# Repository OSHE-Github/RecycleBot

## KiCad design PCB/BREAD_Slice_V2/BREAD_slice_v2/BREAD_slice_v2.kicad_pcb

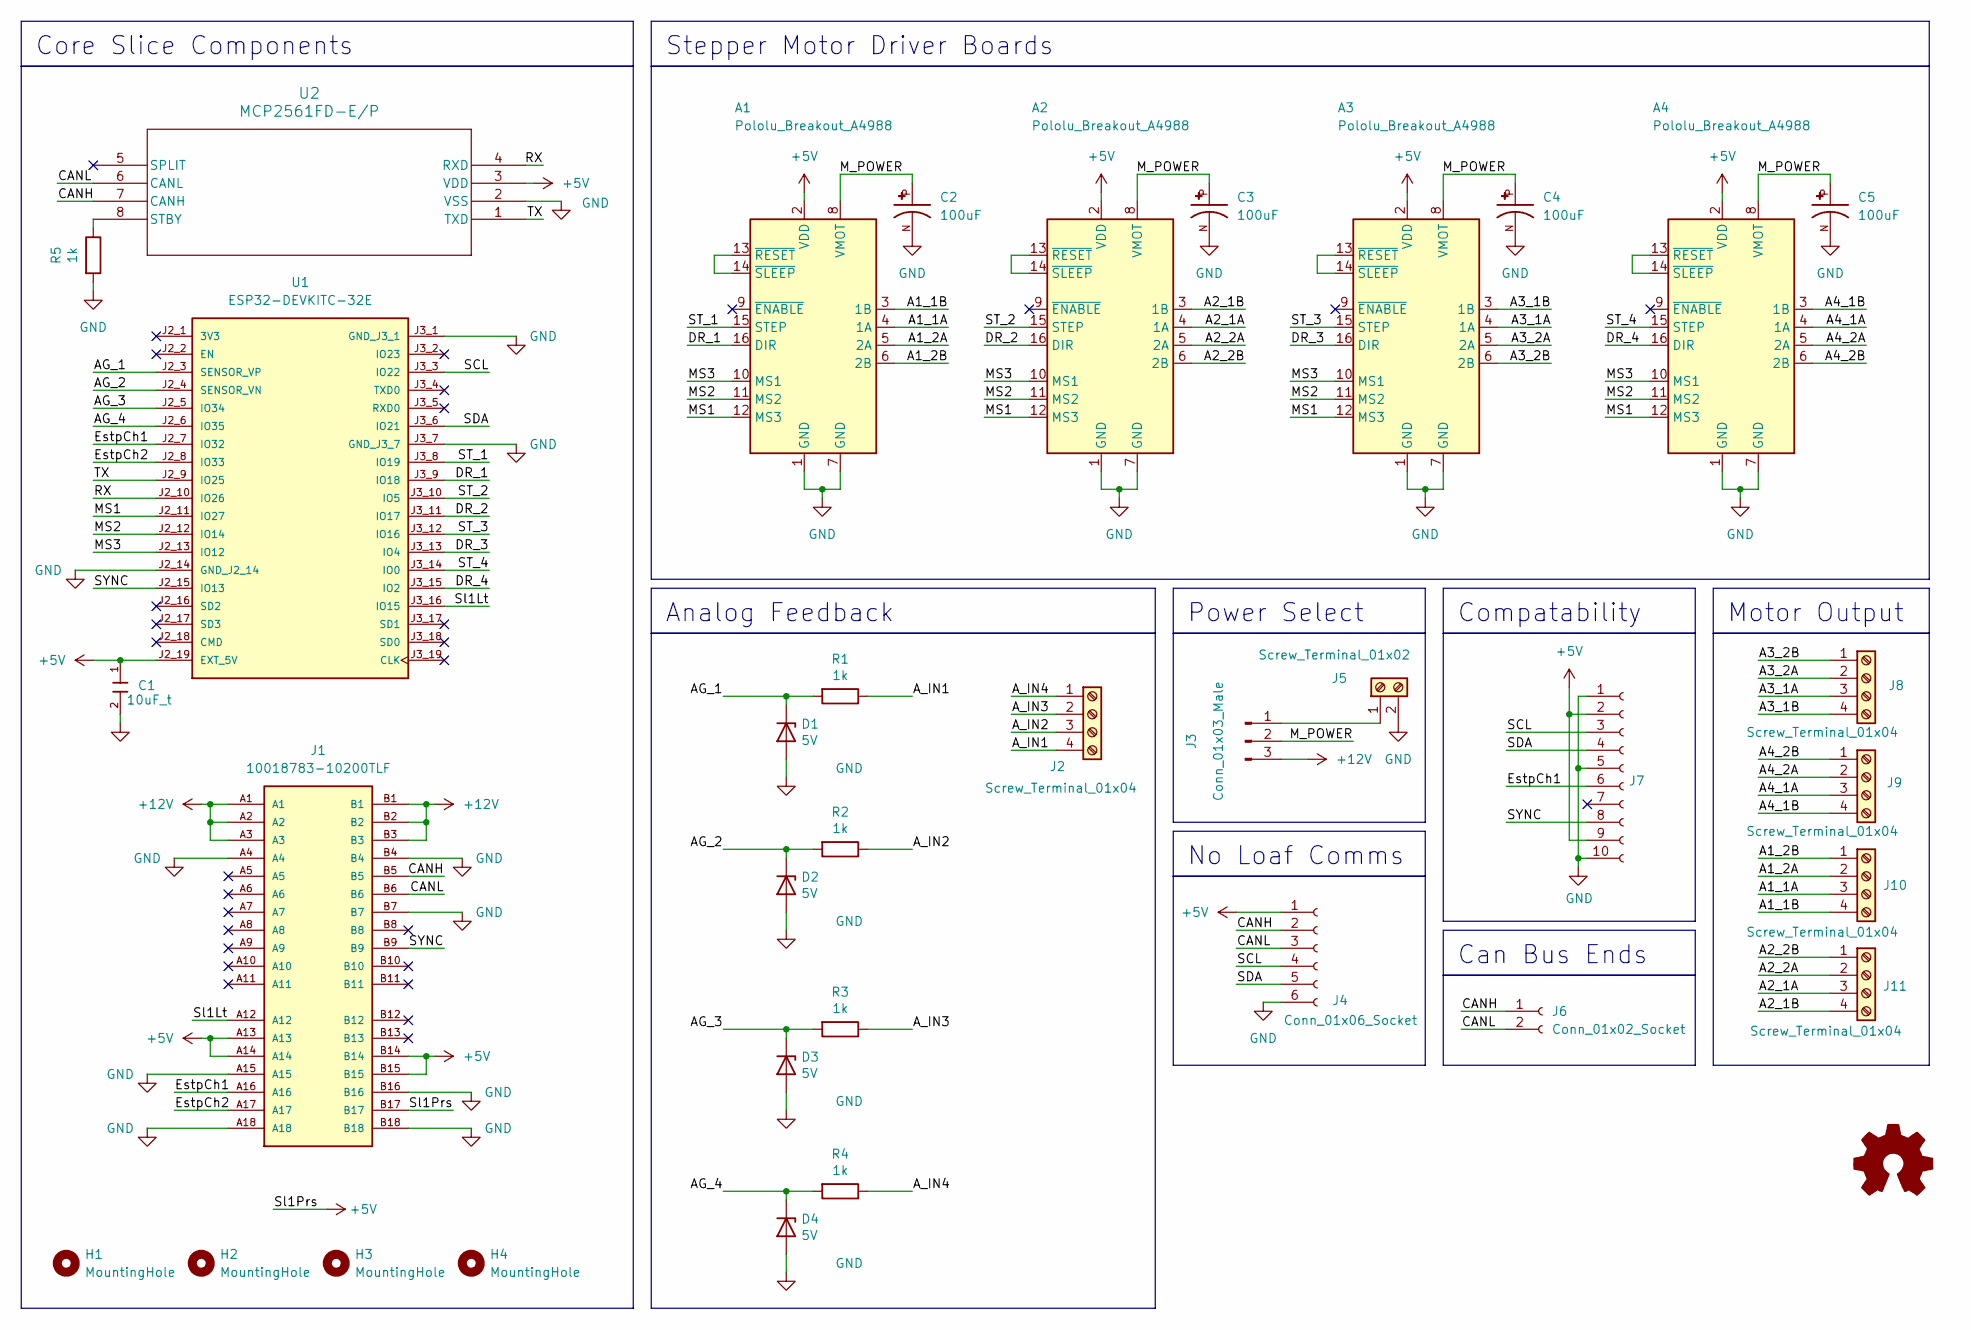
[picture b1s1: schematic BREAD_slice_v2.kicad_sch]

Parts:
A1, A2, A3, A4: Pololu_Breakout_A4988; Pololu_Breakout-16_15.2x20.3mm
C1: 10uF_t; C1206; Part # T491C106K025AT
C2, C3, C4, C5: 100uF; CAPPRD500W60D1000H1250; PARTREV 20-DEC-19
D1, D2, D3, D4: 5V; D_1206_3216Metric_Pad1.42x1.75mm_HandSolder
H1, H2, H3, H4: MountingHole; MountingHole_3.2mm_M3_DIN965_Pad
J1: 10018783-10200TLF; BUS_PCIexpress_x1; PARTREV Z
J2, J8, J9, J10, J11: Screw_Terminal_01x04; TerminalBlock_TE_282834-4_1x04_P2.54mm_Horizontal
J3: Conn_01x03_Male; PinSocket_1x03_P2.54mm_Vertical
J4: Conn_01x06_Socket; PinSocket_1x06_P2.54mm_Horizontal
J5: Screw_Terminal_01x02; TerminalBlock_TE_282834-2_1x02_P2.54mm_Horizontal
J6: Conn_01x02_Socket; PinSocket_1x02_P2.54mm_Vertical
J7: Conn_01x10_Socket; PinSocket_1x10_P2.54mm_Horizontal
Logo1: Logo_Open_Hardware_Small; OSHW-Symbol_6.7x6mm_SilkScreen
R1, R2, R3, R4, R5: 1k; R_1206_3216Metric_Pad1.30x1.75mm_HandSolder
U1: ESP32-DEVKITC-32E; MODULE_ESP32-DEVKITC-32E; PARTREV 1.4
U2: MCP2561FD-E/P; PDIP8_300MC_MCH

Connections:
+5V: A1.2 (VDD), A2.2 (VDD), A3.2 (VDD), A4.2 (VDD), C1.1, J1.A13, J1.A14, J1.B14, J1.B15, J1.B17, J4.1, J7.2, J7.9, U1.J2_19 (EXT_5V), U2.3 (VDD)
+12V: J1.A1, J1.A2, J1.A3, J1.B1, J1.B2, J1.B3, J3.3
/A1_1A: A1.4 (1A), J10.3
/A1_1B: A1.3 (1B), J10.4
/A1_2A: A1.5 (2A), J10.2
/A1_2B: A1.6 (2B), J10.1
/A2_1A: A2.4 (1A), J11.3
/A2_1B: A2.3 (1B), J11.4
/A2_2A: A2.5 (2A), J11.2
/A2_2B: A2.6 (2B), J11.1
/A3_1A: A3.4 (1A), J8.3
/A3_1B: A3.3 (1B), J8.4
/A3_2A: A3.5 (2A), J8.2
/A3_2B: A3.6 (2B), J8.1
/A4_1A: A4.4 (1A), J9.3
/A4_1B: A4.3 (1B), J9.4
/A4_2A: A4.5 (2A), J9.2
/A4_2B: A4.6 (2B), J9.1
/AG_1: D1.1 (K), R1.2, U1.J2_3 (SENSOR_VP)
/AG_2: D2.1 (K), R2.2, U1.J2_4 (SENSOR_VN)
/AG_3: D3.1 (K), R3.2, U1.J2_5 (IO34)
/AG_4: D4.1 (K), R4.2, U1.J2_6 (IO35)
/A_IN1: J2.4, R1.1
/A_IN2: J2.3, R2.1
/A_IN3: J2.2, R3.1
/A_IN4: J2.1, R4.1
/CANH: J1.B5, J4.2, J6.1, U2.7 (CANH)
/CANL: J1.B6, J4.3, J6.2, U2.6 (CANL)
/DR_1: A1.16 (DIR), U1.J3_9 (IO18)
/DR_2: A2.16 (DIR), U1.J3_11 (IO17)
/DR_3: A3.16 (DIR), U1.J3_13 (IO4)
/DR_4: A4.16 (DIR), U1.J3_15 (IO2)
/EstpCh1: J1.A16, J7.6, U1.J2_7 (IO32)
/EstpCh2: J1.A17, U1.J2_8 (IO33)
/MS1: A1.12 (MS3), A2.12 (MS3), A3.12 (MS3), A4.12 (MS3), U1.J2_11 (IO27)
/MS2: A1.11 (MS2), A2.11 (MS2), A3.11 (MS2), A4.11 (MS2), U1.J2_12 (IO14)
/MS3: A1.10 (MS1), A2.10 (MS1), A3.10 (MS1), A4.10 (MS1), U1.J2_13 (IO12)
/M_POWER: A1.8 (VMOT), A2.8 (VMOT), A3.8 (VMOT), A4.8 (VMOT), C2.P, C3.P, C4.P, C5.P, J3.2
/RX: U1.J2_10 (IO26), U2.4 (RXD)
/SCL: J4.4, J7.3, U1.J3_3 (IO22)
/SDA: J4.5, J7.4, U1.J3_6 (IO21)
/ST_1: A1.15 (STEP), U1.J3_8 (IO19)
/ST_2: A2.15 (STEP), U1.J3_10 (IO5)
/ST_3: A3.15 (STEP), U1.J3_12 (IO16)
/ST_4: A4.15 (STEP), U1.J3_14 (IO0)
/SYNC: J1.B9, J7.8, U1.J2_15 (IO13)
/Sl1Lt: J1.A12, U1.J3_16 (IO15)
/TX: U1.J2_9 (IO25), U2.1 (TXD)
GND: A1.1 (GND), A1.7 (GND), A2.1 (GND), A2.7 (GND), A3.1 (GND), A3.7 (GND), A4.1 (GND), A4.7 (GND), C1.2, C2.N, C3.N, C4.N, C5.N, D1.2 (A), D2.2 (A), D3.2 (A), D4.2 (A), J1.A4, J1.A15, J1.A18, J1.B4, J1.B7, J1.B16, J1.B18, J4.6, J5.2, J7.1, J7.5, J7.10, R5.2, U1.J2_14 (GND_J2_14), U1.J3_1 (GND_J3_1), U1.J3_7 (GND_J3_7), U2.2 (VSS)
unnamed: A1.13 (~RESET), A1.14 (~SLEEP)
unnamed: A2.13 (~RESET), A2.14 (~SLEEP)
unnamed: A3.13 (~RESET), A3.14 (~SLEEP)
unnamed: A4.13 (~RESET), A4.14 (~SLEEP)
unnamed: J3.1, J5.1
unnamed: R5.1, U2.8 (STBY)

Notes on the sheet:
Analog Feedback
Compatability
Stepper Motor Driver Boards
Can Bus Ends
Motor Output
Power Select
Core Slice Components
No Loaf Comms

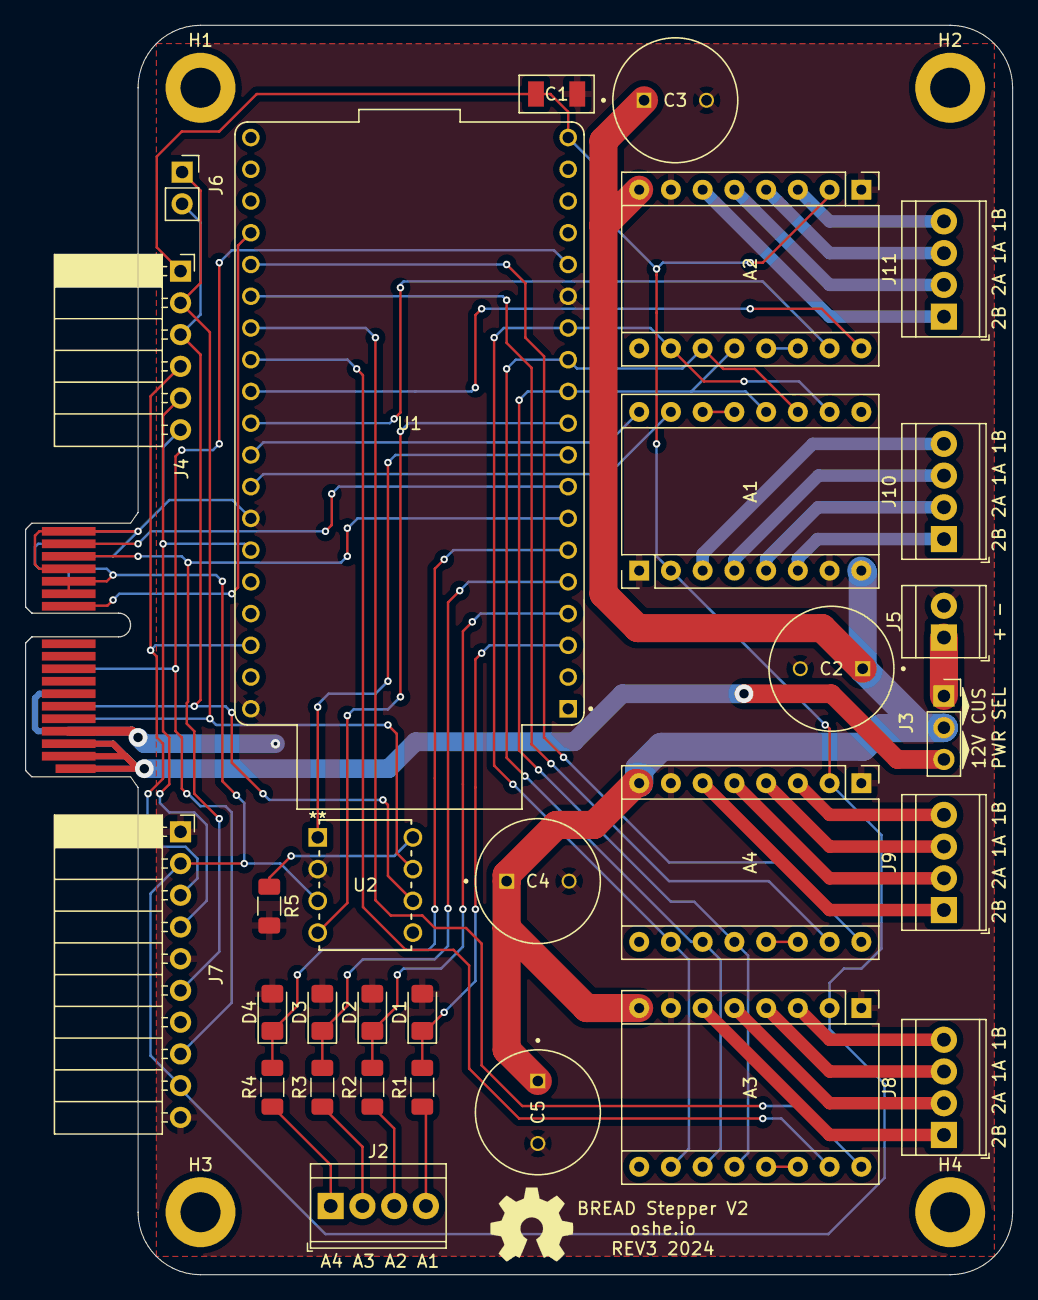
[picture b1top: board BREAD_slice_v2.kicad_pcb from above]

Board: 2 copper layers, 79.0 x 100.0 mm, 36 parts (1 on the bottom side), 55 nets.

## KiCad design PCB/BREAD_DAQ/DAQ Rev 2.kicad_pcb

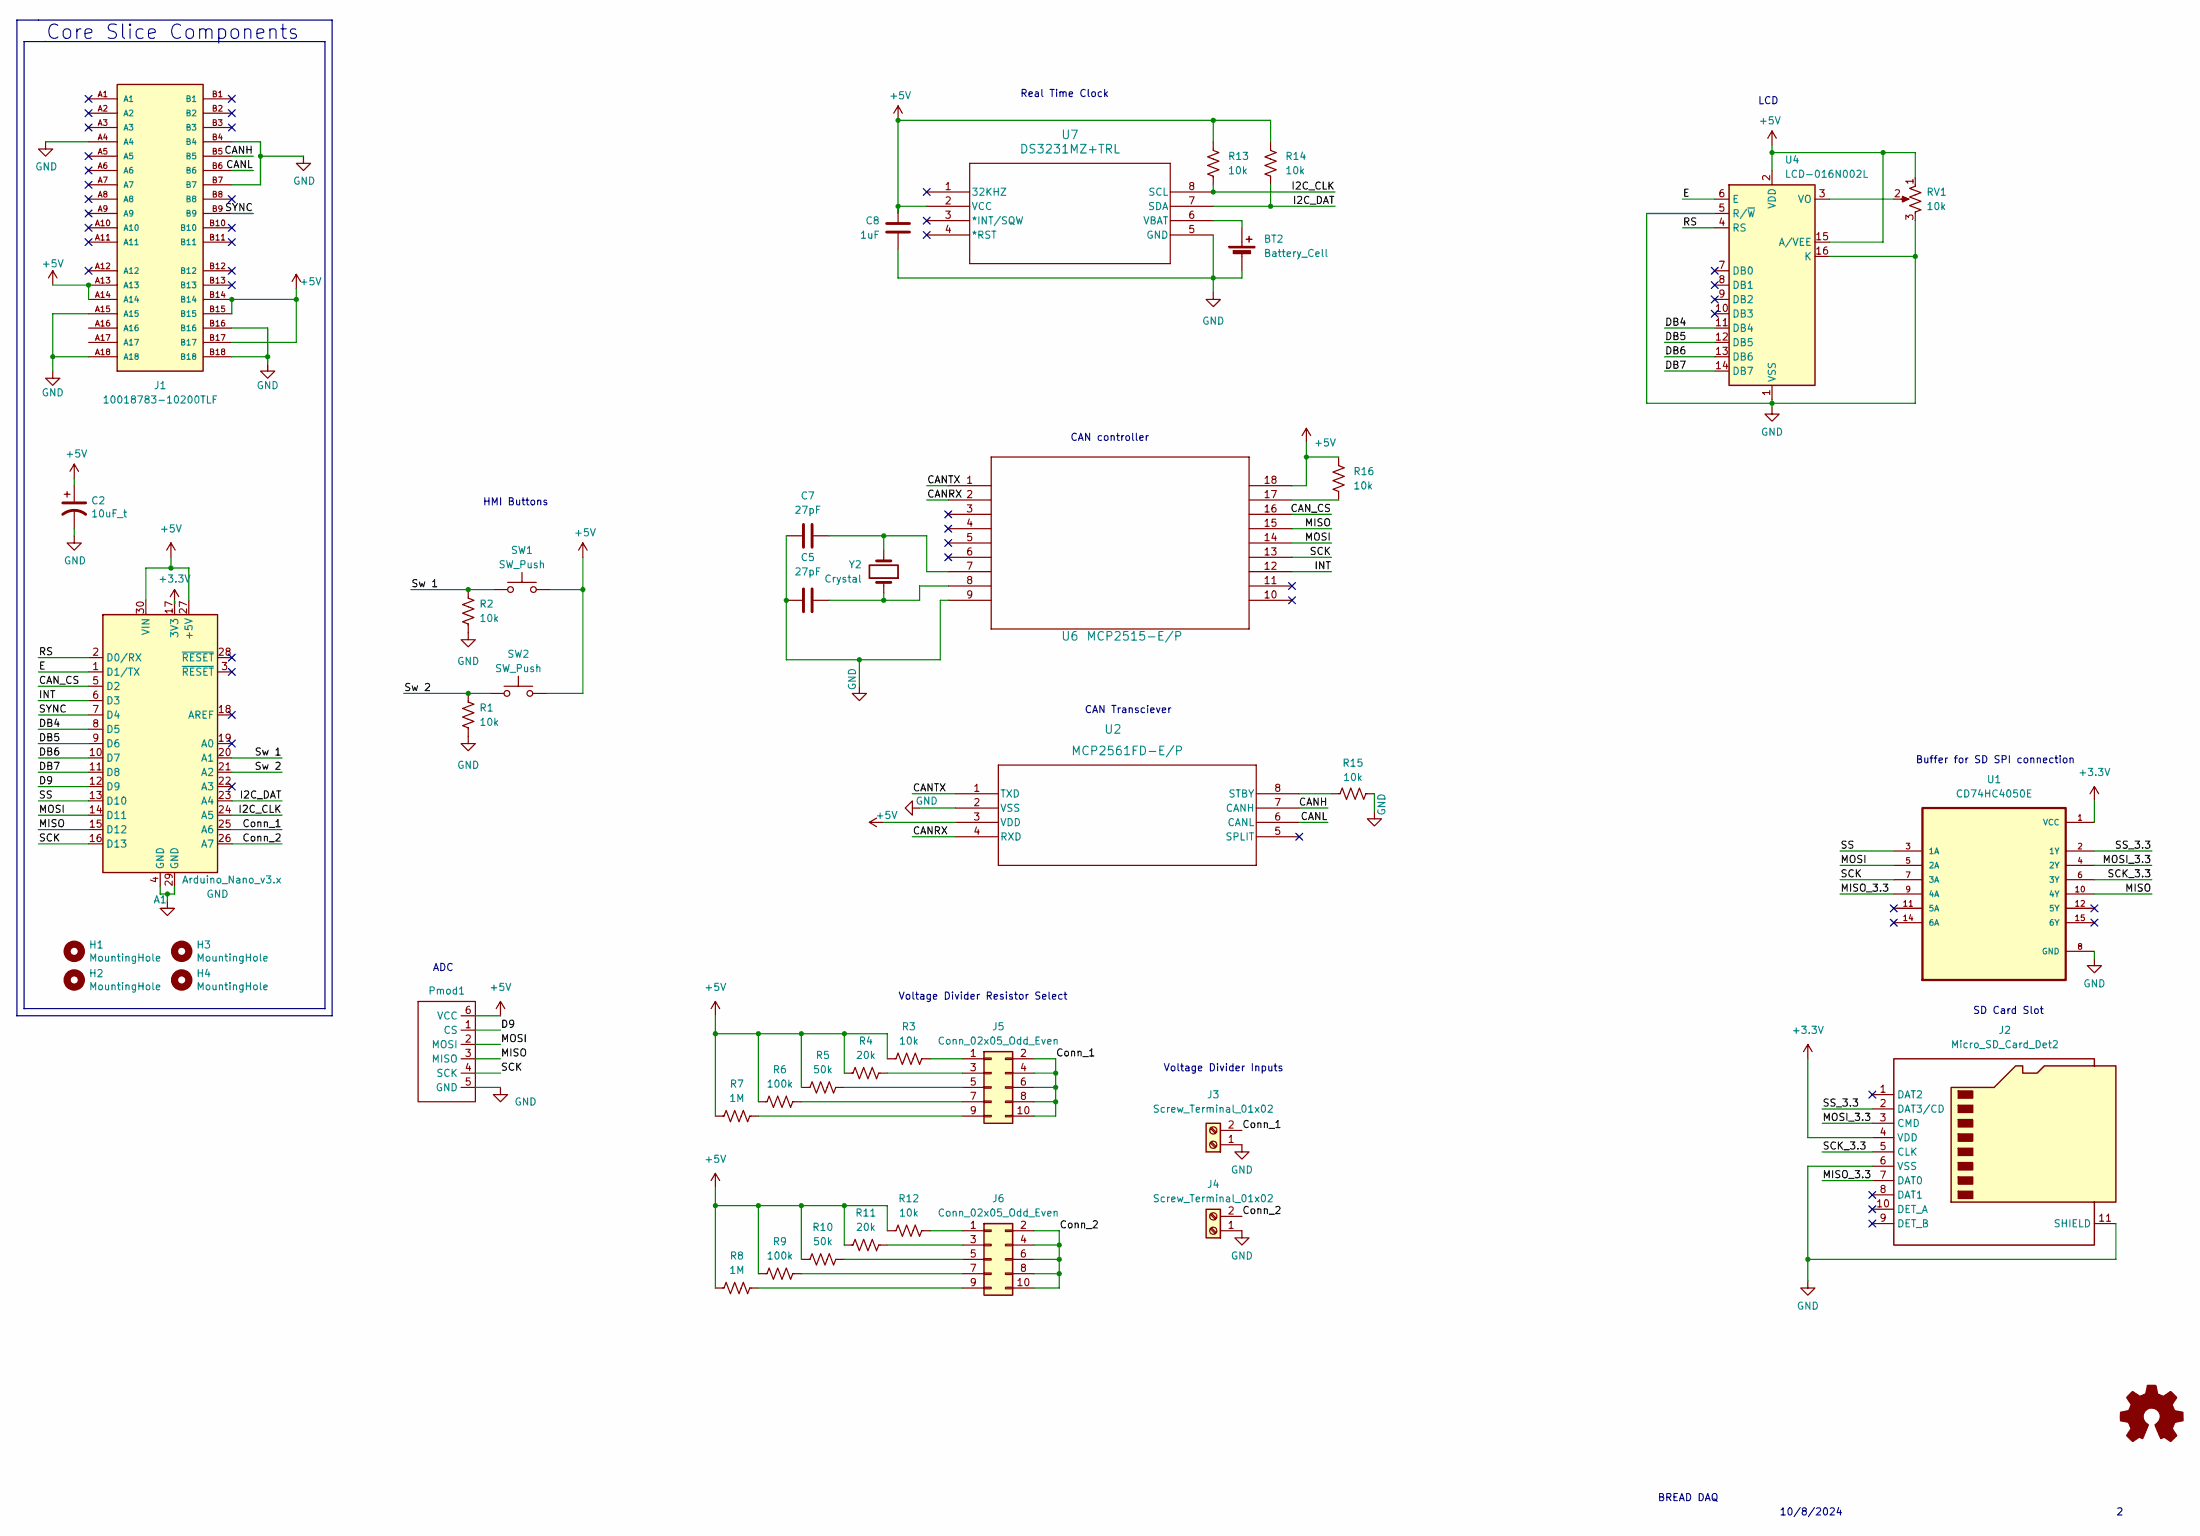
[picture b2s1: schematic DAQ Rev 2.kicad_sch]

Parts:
A1: Arduino_Nano_v3.x; Arduino_Nano
BT2: Battery_Cell; BatteryHolder_Keystone_3034_1x20mm
C2: 10uF_t; C_1206_3216Metric_Pad1.33x1.80mm_HandSolder; Part # T491C106K025AT
C5, C7: 27pF; C_1206_3216Metric_Pad1.33x1.80mm_HandSolder
C8: 1uF; C_1206_3216Metric_Pad1.33x1.80mm_HandSolder
H1, H2, H3, H4: MountingHole; MountingHole_3.2mm_M3_DIN965_Pad
J1: 10018783-10200TLF; BUS_PCIexpress_x1; PARTREV Z
J2: Micro_SD_Card_Det2; 104031-0811_MOL
J3, J4: Screw_Terminal_01x02; TerminalBlock_Phoenix_MKDS-1,5-2_1x02_P5.00mm_Horizontal
J5, J6: Conn_02x05_Odd_Even; PinHeader_2x05_P2.54mm_Vertical
Logo1: Logo_Open_Hardware_Small; OSHW-Symbol_6.7x6mm_SilkScreen
Pmod1: PinSocket_1x06_P2.54mm_Horizontal
R1, R2, R3, R12, R13, R14, R15, R16: 10k; R_1206_3216Metric_Pad1.30x1.75mm_HandSolder
R4, R11: 20k; R_1206_3216Metric_Pad1.30x1.75mm_HandSolder
R5, R10: 50k; R_1206_3216Metric_Pad1.30x1.75mm_HandSolder
R6, R9: 100k; R_1206_3216Metric_Pad1.30x1.75mm_HandSolder
R7, R8: 1M; R_1206_3216Metric_Pad1.30x1.75mm_HandSolder
RV1: 10k; Potentiometer_Bourns_3386P_Vertical
SW1, SW2: SW_Push; SW_PUSH_6mm
U1: CD74HC4050E; DIP794W45P254L1969H508Q16
U2: MCP2561FD-E/P; PDIP8_300MC_MCH
U4: LCD-016N002L; WC1602A-No holes
U6: MCP2515-E/P; PDIP18_300MC_MCH
U7: DS3231MZ+TRL; 21-0041B_8_MXM
Y2: Crystal; XTAL_ECS-160-20-3X-TR

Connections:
+3.3V: A1.17 (3V3), J2.4 (VDD), U1.1 (VCC)
+5V: A1.27 (+5V), A1.30 (VIN), C2.1, C8.1, J1.A13, J1.A14, J1.B14, J1.B15, J1.B17, Pmod1.6 (VCC), R3.2, R4.2, R5.2, R6.2, R7.2, R8.2, R9.2, R10.2, R11.2, R12.2, R13.1, R14.1, R16.2, RV1.1, SW1.2, SW2.2, U2.3 (VDD), U4.2 (VDD), U4.15 (A/VEE), U6.18, U7.2 (VCC)
/CANH: J1.B5, U2.7 (CANH)
/CANL: J1.B6, U2.6 (CANL)
/CANRX: U2.4 (RXD), U6.2
/CANTX: U2.1 (TXD), U6.1
/CAN_CS: A1.5 (D2), U6.16
/Conn_1: A1.25 (A6), J3.2, J5.2, J5.4, J5.6, J5.8, J5.10
/Conn_2: A1.26 (A7), J4.2, J6.2, J6.4, J6.6, J6.8, J6.10
/D9: A1.12 (D9), Pmod1.1 (CS)
/DB4: A1.8 (D5), U4.11 (DB4)
/DB5: A1.9 (D6), U4.12 (DB5)
/DB6: A1.10 (D7), U4.13 (DB6)
/DB7: A1.11 (D8), U4.14 (DB7)
/E: A1.1 (D1/TX), U4.6 (E)
/I2C_CLK: A1.24 (A5), R13.2, U7.8 (SCL)
/I2C_DAT: A1.23 (A4), R14.2, U7.7 (SDA)
/INT: A1.6 (D3), U6.12
/MISO: A1.15 (D12), Pmod1.3 (MISO), U1.10 (4Y), U6.15
/MISO_3.3: J2.7 (DAT0), U1.9 (4A)
/MOSI: A1.14 (D11), Pmod1.2 (MOSI), U1.5 (2A), U6.14
/MOSI_3.3: J2.3 (CMD), U1.4 (2Y)
/RS: A1.2 (D0/RX), U4.4 (RS)
/SCK: A1.16 (D13), Pmod1.4 (SCK), U1.7 (3A), U6.13
/SCK_3.3: J2.5 (CLK), U1.6 (3Y)
/SS: A1.13 (D10), U1.3 (1A)
/SS_3.3: J2.2 (DAT3/CD), U1.2 (1Y)
/SYNC: A1.7 (D4), J1.B9
/Sw 1: A1.20 (A1), R2.2, SW1.1
/Sw 2: A1.21 (A2), R1.2, SW2.1
GND: A1.4 (GND), A1.29 (GND), BT2.2 (-), C2.2, C5.2, C7.1, C8.2, J1.A4, J1.A15, J1.A18, J1.B4, J1.B7, J1.B16, J1.B18, J2.6 (VSS), J2.11 (SHIELD), J3.1, J4.1, Pmod1.5 (GND), R1.1, R2.1, R15.1, RV1.3, U1.8 (GND), U2.2 (VSS), U4.1 (VSS), U4.5 (R/~W), U4.16 (K), U6.9, U7.5 (GND)
unnamed: BT2.1 (+), U7.6 (VBAT)
unnamed: C5.1, U6.8, Y2.1
unnamed: C7.2, U6.7, Y2.2
unnamed: J5.1, R3.1
unnamed: J5.3, R4.1
unnamed: J5.5, R5.1
unnamed: J5.7, R6.1
unnamed: J5.9, R7.1
unnamed: J6.1, R12.1
unnamed: J6.3, R11.1
unnamed: J6.5, R10.1
unnamed: J6.7, R9.1
unnamed: J6.9, R8.1
unnamed: R16.1, U6.17
unnamed: R15.2, U2.8 (STBY)
unnamed: RV1.2, U4.3 (VO)

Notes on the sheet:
Real Time Clock
HMI Buttons
ADC
Voltage Divider Inputs
10/8/2024
BREAD DAQ
Buffer for SD SPI connection
Core Slice Components
CAN Transciever
Voltage Divider Resistor Select
SD Card Slot
LCD
CAN controller

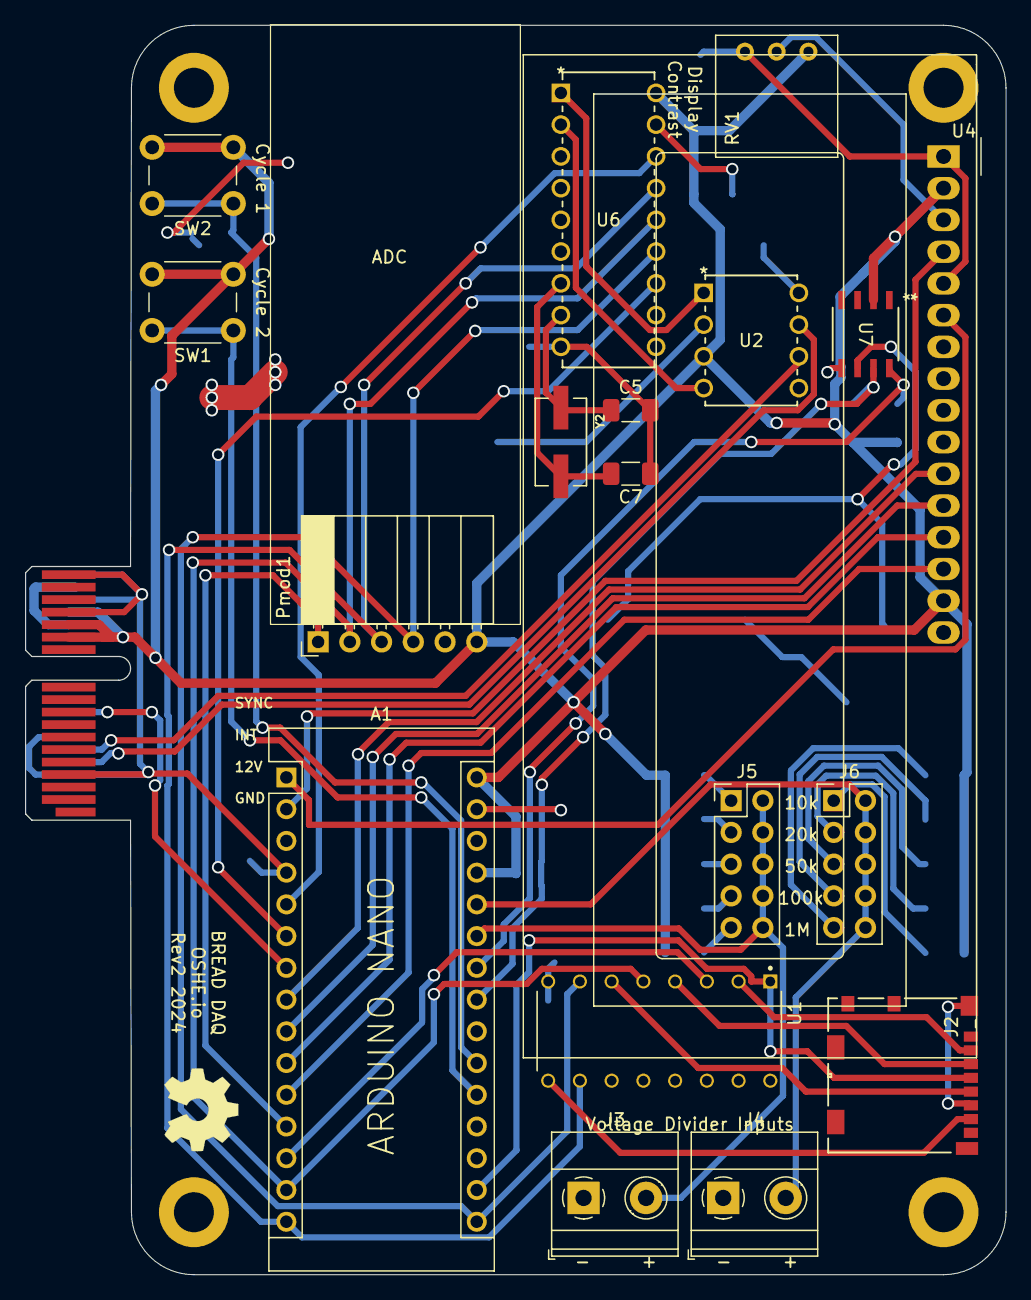
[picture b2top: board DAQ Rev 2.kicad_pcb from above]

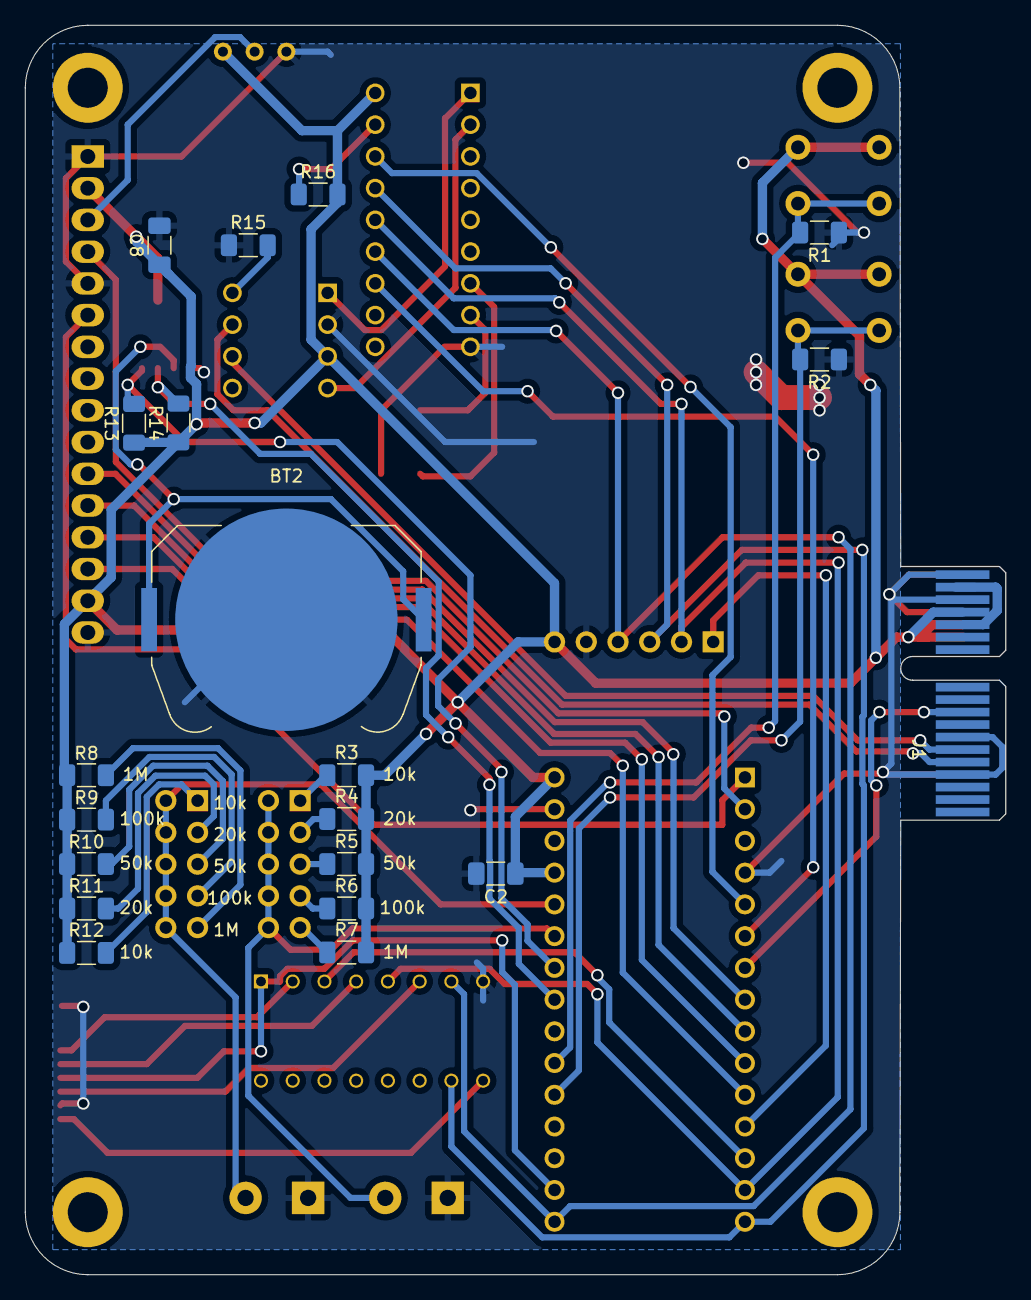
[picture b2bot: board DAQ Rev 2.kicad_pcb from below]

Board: 2 copper layers, 78.5 x 100.0 mm, 43 parts (20 on the bottom side), 47 nets.

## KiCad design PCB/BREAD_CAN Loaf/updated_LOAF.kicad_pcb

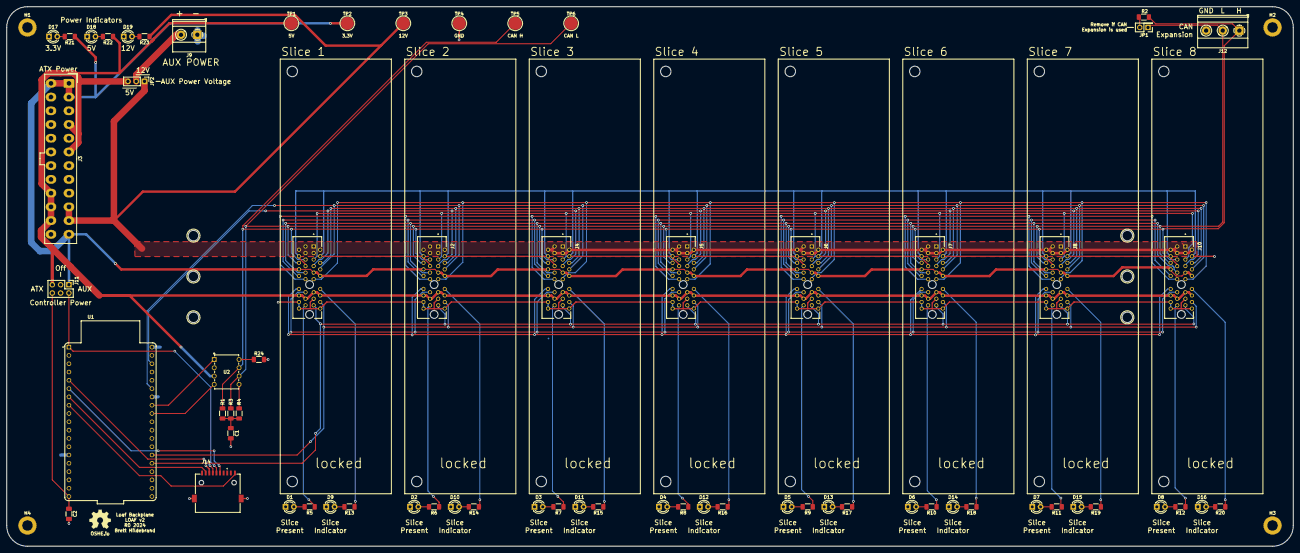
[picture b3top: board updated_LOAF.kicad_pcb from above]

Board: 2 copper layers, 393.7 x 165.1 mm, 91 parts (0 on the bottom side), 66 nets.

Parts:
C1: 4700pF; C_1206_3216Metric_Pad1.33x1.80mm_HandSolder
C2: 10uF_t; C_1206_3216Metric_Pad1.33x1.80mm_HandSolder
D1, D2, D3, D4, D5, D6, D7, D8, D9, D10, D11, D12, D13, D14, D15, D16, D17, D18, D19: LED; LED_D3.0mm
DRA1, DRA2: DIN_Rail_Adapter; DINRailAdapter_3xM3_PhoenixContact_1201578
H1, H2, H3, H4: MountingHole; MountingHole_3.2mm_M3_DIN965_Pad
H5, H6, H7, H8, H9, H10, H11, H12, H13, H14, H15, H16, H17, H18, H19, H20: MountingHole; MountingHole_3.2mm_M3
J1, J2, J4, J5, J6, J7, J8, J10: 10018783-10200TLF; AMPHENOL_10018783-10200TLF
J3: ATX-24; Molex_Mini-Fit_Jr_5566-24A_2x12_P4.20mm_Vertical
J9: Screw_Terminal_01x02; TerminalBlock_Phoenix_MKDS-1,5-2_1x02_P5.00mm_Horizontal
J11: Conn_02x03_Odd_Even; PinHeader_2x03_P2.54mm_Vertical
J12: Screw_Terminal_01x03; TerminalBlock_Phoenix_MKDS-1,5-3-5.08_1x03_P5.08mm_Horizont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
J14: MSD-11-A; CUI_MSD-11-A
JP1: Jumper_2_Bridged; PinHeader_2x01_P2.54mm_Vertical
JP2: Jumper_3_Bridged12; PinHeader_1x03_P2.54mm_Vertical
Logo1: Logo_Open_Hardware_Small; OSHW-Symbol_6.7x6mm_SilkScreen
R1, R3: 60; R_1206_3216Metric_Pad1.30x1.75mm_HandSolder
R2: 120; R_1206_3216Metric_Pad1.30x1.75mm_HandSolder
R4: 300; R_1206_3216Metric_Pad1.30x1.75mm_HandSolder
R5, R6, R7, R8, R9, R10, R11, R12, R13, R14, R15, R16, R17, R18, R19, R20, R21, R22, R23: R_US; R_1206_3216Metric_Pad1.30x1.75mm_HandSolder
R24: 10k; R_1206_3216Metric_Pad1.30x1.75mm_HandSolder
TP1, TP2, TP3, TP4, TP5, TP6: TestPoint; TestPoint_Pad_D4.0mm
U1: ESP32-DEVKITC-32E; MODULE_ESP32-DEVKITC-32E
U2: MCP2561FD-E/P; PDIP8_300MC_MCH

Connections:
+3.3V: J1.A9, J1.A10, J1.B8, J2.A9, J2.A10, J2.B8, J3.1 (+3.3V), J3.2 (+3.3V), J3.12 (+3.3V), J3.13 (+3.3V), J4.A9, J4.A10, J4.B8, J5.A9, J5.A10, J5.B8, J6.A9, J6.A10, J6.B8, J7.A9, J7.A10, J7.B8, J8.A9, J8.A10, J8.B8, J10.A9, J10.A10, J10.B8, J11.1, R21.1, TP2.1
+5V: J1.A13, J1.A14, J1.B14, J1.B15, J2.A13, J2.A14, J2.B14, J2.B15, J3.4 (+5V), J3.6 (+5V), J3.21 (+5V), J3.22 (+5V), J3.23 (+5V), J4.A13, J4.A14, J4.B14, J4.B15, J5.A13, J5.A14, J5.B14, J5.B15, J6.A13, J6.A14, J6.B14, J6.B15, J7.A13, J7.A14, J7.B14, J7.B15, J8.A13, J8.A14, J8.B14, J8.B15, J10.A13, J10.A14, J10.B14, J10.B15, J11.5, JP2.3 (B), R22.1, TP1.1, U2.3 (VDD)
+12V: J1.A1, J1.A2, J1.A3, J1.B1, J1.B2, J1.B3, J2.A1, J2.A2, J2.A3, J2.B1, J2.B2, J2.B3, J3.10 (+12V), J3.11 (+12V), J4.A1, J4.A2, J4.A3, J4.B1, J4.B2, J4.B3, J5.A1, J5.A2, J5.A3, J5.B1, J5.B2, J5.B3, J6.A1, J6.A2, J6.A3, J6.B1, J6.B2, J6.B3, J7.A1, J7.A2, J7.A3, J7.B1, J7.B2, J7.B3, J8.A1, J8.A2, J8.A3, J8.B1, J8.B2, J8.B3, J10.A1, J10.A2, J10.A3, J10.B1, J10.B2, J10.B3, JP2.1 (A), R23.1, TP3.1
/CANH: J1.B5, J2.B5, J4.B5, J5.B5, J6.B5, J7.B5, J8.B5, J10.B5, J12.1, R1.1, R2.1, TP5.1, U2.7 (CANH)
/CANL: J1.B6, J2.B6, J4.B6, J5.B6, J6.B6, J7.B6, J8.B6, J10.B6, J12.2, JP1.1 (A), R3.2, TP6.1, U2.6 (CANL)
/EstpCh1: J1.A16, J2.A16, J4.A16, J5.A16, J6.A16, J7.A16, J8.A16, J10.A16, U1.J3_14 (IO0)
/EstpCh2: J1.A17, J2.A17, J4.A17, J5.A17, J6.A17, J7.A17, J8.A17, J10.A17, U1.J3_15 (IO2)
/RX: U1.J3_9 (IO18), U2.4 (RXD)
/SCL: J1.A7, J2.A7, J4.A7, J5.A7, J6.A7, J7.A7, J8.A7, J10.A7, U1.J3_3 (IO22)
/SDA: J1.A8, J2.A8, J4.A8, J5.A8, J6.A8, J7.A8, J8.A8, J10.A8, U1.J3_6 (IO21)
/SPLIT: R4.1, U2.5 (SPLIT)
/STBY: R24.1, U2.8 (STBY)
/SYNC: J1.B9, J2.B9, J4.B9, J5.B9, J6.B9, J7.B9, J8.B9, J10.B9
/Spare1: J1.B10, J2.B10, J4.B10, J5.B10, J6.B10, J7.B10, J8.B10, J10.B10
/Spare2: J1.B11, J2.B11, J4.B11, J5.B11, J6.B11, J7.B11, J8.B11, J10.B11
/Spare3: J1.B12, J2.B12, J4.B12, J5.B12, J6.B12, J7.B12, J8.B12, J10.B12
/Spare4: J1.B13, J2.B13, J4.B13, J5.B13, J6.B13, J7.B13, J8.B13, J10.B13
/Spare5: J1.A5, J2.A5, J4.A5, J5.A5, J6.A5, J7.A5, J8.A5, J10.A5
/Spare6: J1.A6, J2.A6, J4.A6, J5.A6, J6.A6, J7.A6, J8.A6, J10.A6
/Spare7: J1.A11, J2.A11, J4.A11, J5.A11, J6.A11, J7.A11, J8.A11, J10.A11
/TX: U1.J3_8 (IO19), U2.1 (TXD)
CLK: J14.P5 (CLK), U1.J2_5 (IO34)
CS: J14.CD, U1.J2_8 (IO33)
ESP 3V3: J11.2, J14.P4 (VDD), U1.J2_1 (3V3)
ESP 5V: C2.1, J11.6, U1.J2_19 (EXT_5V)
GND: C1.2, C2.2, D1.1 (K), D2.1 (K), D3.1 (K), D4.1 (K), D5.1 (K), D6.1 (K), D7.1 (K), D8.1 (K), D9.1 (K), D10.1 (K), D11.1 (K), D12.1 (K), D13.1 (K), D14.1 (K), D15.1 (K), D16.1 (K), D17.1 (K), D18.1 (K), D19.1 (K), J1.A4, J1.A15, J1.A18, J1.B4, J1.B7, J1.B16, J1.B18, J2.A4, J2.A15, J2.A18, J2.B4, J2.B7, J2.B16, J2.B18, J3.3 (GND), J3.5 (GND), J3.7 (GND), J3.15 (GND), J3.17 (GND), J3.18 (GND), J3.19 (GND), J3.24 (GND), J4.A4, J4.A15, J4.A18, J4.B4, J4.B7, J4.B16, J4.B18, J5.A4, J5.A15, J5.A18, J5.B4, J5.B7, J5.B16, J5.B18, J6.A4, J6.A15, J6.A18, J6.B4, J6.B7, J6.B16, J6.B18, J7.A4, J7.A15, J7.A18, J7.B4, J7.B7, J7.B16, J7.B18, J8.A4, J8.A15, J8.A18, J8.B4, J8.B7, J8.B16, J8.B18, J9.1, J10.A4, J10.A15, J10.A18, J10.B4, J10.B7, J10.B16, J10.B18, J12.3, J14.G1 (COVER_GND), J14.G2 (COVER_GND__1), J14.P6 (VSS), R24.2, TP4.1, U1.J2_14 (GND_J2_14), U1.J3_1 (GND_J3_1), U1.J3_7 (GND_J3_7), U2.2 (VSS)
MISO: J14.P7 (DAT0), U1.J2_7 (IO32)
MOSI: J14.P3 (CMD), U1.J2_6 (IO35)
unnamed: C1.1, R1.2, R3.1, R4.2
unnamed: D1.2 (A), R5.2
unnamed: D2.2 (A), R6.2
unnamed: D3.2 (A), R7.2
unnamed: D4.2 (A), R8.2
unnamed: D5.2 (A), R9.2
unnamed: D6.2 (A), R10.2
unnamed: D7.2 (A), R11.2
unnamed: D8.2 (A), R12.2
unnamed: D9.2 (A), R13.2
unnamed: D10.2 (A), R14.2
unnamed: D11.2 (A), R15.2
unnamed: D12.2 (A), R16.2
unnamed: D13.2 (A), R17.2
unnamed: D14.2 (A), R18.2
unnamed: D15.2 (A), R19.2
unnamed: D16.2 (A), R20.2
unnamed: D17.2 (A), R21.2
unnamed: D18.2 (A), R22.2
unnamed: D19.2 (A), R23.2
unnamed: J9.2, JP2.2 (C)
unnamed: JP1.2 (B), R2.2
Sl1Lt: J1.A12, R13.1
Sl1Prs: J1.B17, R5.1
Sl2Lt: J2.A12, R14.1
Sl2Prs: J2.B17, R6.1
Sl3Lt: J4.A12, R15.1
Sl3Prs: J4.B17, R7.1
Sl4Lt: J5.A12, R16.1
Sl4Prs: J5.B17, R8.1
Sl5Lt: J6.A12, R17.1
Sl5Prs: J6.B17, R9.1
Sl6Lt: J7.A12, R18.1
Sl6Prs: J7.B17, R10.1
Sl7Lt: J8.A12, R19.1
Sl7Prs: J8.B17, R11.1
Sl8Lt: J10.A12, R20.1
Sl8Prs: J10.B17, R12.1

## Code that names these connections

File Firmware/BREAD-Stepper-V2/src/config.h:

#ifndef CONFIG_H
#define CONFIG_H

#include "BREAD_CAN_Slices.h"

//???????????????????????
#define NUM_DCMT_SLICES 8
#define NUM_RLHT_SLICES 8
#define NUM_PHDO_SLICES 2
//???????????????????????

// ********************
// * Universal Macros *
// ********************

#define ESTOP1  36
#define SYNC    15

// Analog Feedback
#define AG_1    32
#define AG_2    33
#define AG_3    25
#define AG_4    26

// Stepper Motor Driver Pins
#define MS1     27 // +---------------+
#define MS2     14 // | Microstepping |
#define MS3     12 // +---------------+
#define ST_1    19 // +-----------+
#define DR_1    18 // |           |
#define ST_2    5  // |  Stepper  |
#define DR_2    17 // |   Motor   |
#define ST_3    16 // |  Step &   |
#define DR_3    4  // | Direction |
#define ST_4    0  // |           |
#define DR_4    2  // +-----------+

// ***************************
// * Loaf V2 Specific Macros *
// ***************************

// Misc Pins
#define ESTOP2      39
#define SLICE_LED   15

// CAN
#define SLICE_DATA_INTERVAL_MS 1000 // CAN Bus Data Interval
#define CAN_TX 25
#define CAN_RX 26

// ************************************
// * Loaf V1 (Legacy) Specific Macros *
// ************************************

// I2C
#define SDA     21
#define SCL     22

#endif

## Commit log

2025-03-17 Added pictures of build from mid-spring 2025
2025-03-17 renamed pictures for clarity
2025-03-17 Update README.md with pictures of the project
2025-03-17 Migrated PCB and Firmware files to this repo
2025-03-18 added accelstepper library
2025-03-18 that was not supposed to be there :P
2025-03-18 TODO: loop(), update config.h with CAN id
2025-03-18 removed esp time package, was unused
2025-03-18 added BREAD_CAN_Slices.h from DAQ code
2025-03-18 vscode workspace
2025-03-27 fixed can tx/rx on input only pins
2025-03-31 finished? stepper slice
2025-03-31 support for stepper slice and infidel sensor on DAQ
2025-04-10 better tuned control loop to change speed sooner and increment by smaller steps to avoid over and undershooting target diameter
2025-04-10 added support for mm for SD card writing on DAQ
2025-04-12 removed bad vscode workspace file that was broken
2025-04-26 added 3d print files for rewind unit + others, added gitignore for kicad lock files
